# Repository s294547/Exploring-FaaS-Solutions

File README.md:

# EXPLORING FAAS SOLUTION

<div style="margin-left: auto;
            margin-right: auto;
            width: 50%">

|||
|:--:|:--:|
| **Author** | Giulia Bianchi|
| **Contact** | s294547@studenti.polito.it |
</div>

1. [Introduction](#introduction)

## Introduction

This repository, up to now, contains all the data I produced to develop my master thesis. 
Up to now, there are the following folders:
1. [openwhisk](./openwhisk/): it contains whatever I have done related to openwhisk.
2. [microsoft-azure-functions](./microsoft-azure-functions/): it contains whatever I have done/researched related to microsoft azure functions.
3. [AWS-lambda](./AWS-lambda/): it contains whatever I have done/researched related to AWS lambdas.
4. [knative](./knative/): it contains whatever I have done/researched related to knative.
5. [openfaas](./openfaas/):  it contains whatever I have done/researched related to openfaas.
6. [efk](./efk): it contains the informations necessary to develop an efk stack in a kubernetes cluster
7. [helm-charts](./helm-charts): it contains some helm charts.
8. [liquidfaas](./liquidfaas): it contains the KubeConfig file related to the cluster I am using.
9. [SUMMARY](./SUMMARY/): it contains a sumarry of the thesis activity up to now. 
10. [SCHEDA](./SCHEDA/): it contains the files related to the EP8266 board and sensors.

There is another markdown file [discovering-and-comparing-faas-tools](./discovering-and-comparing-faas-tools.md) in which I made a comparison between the analyzed faas tools.

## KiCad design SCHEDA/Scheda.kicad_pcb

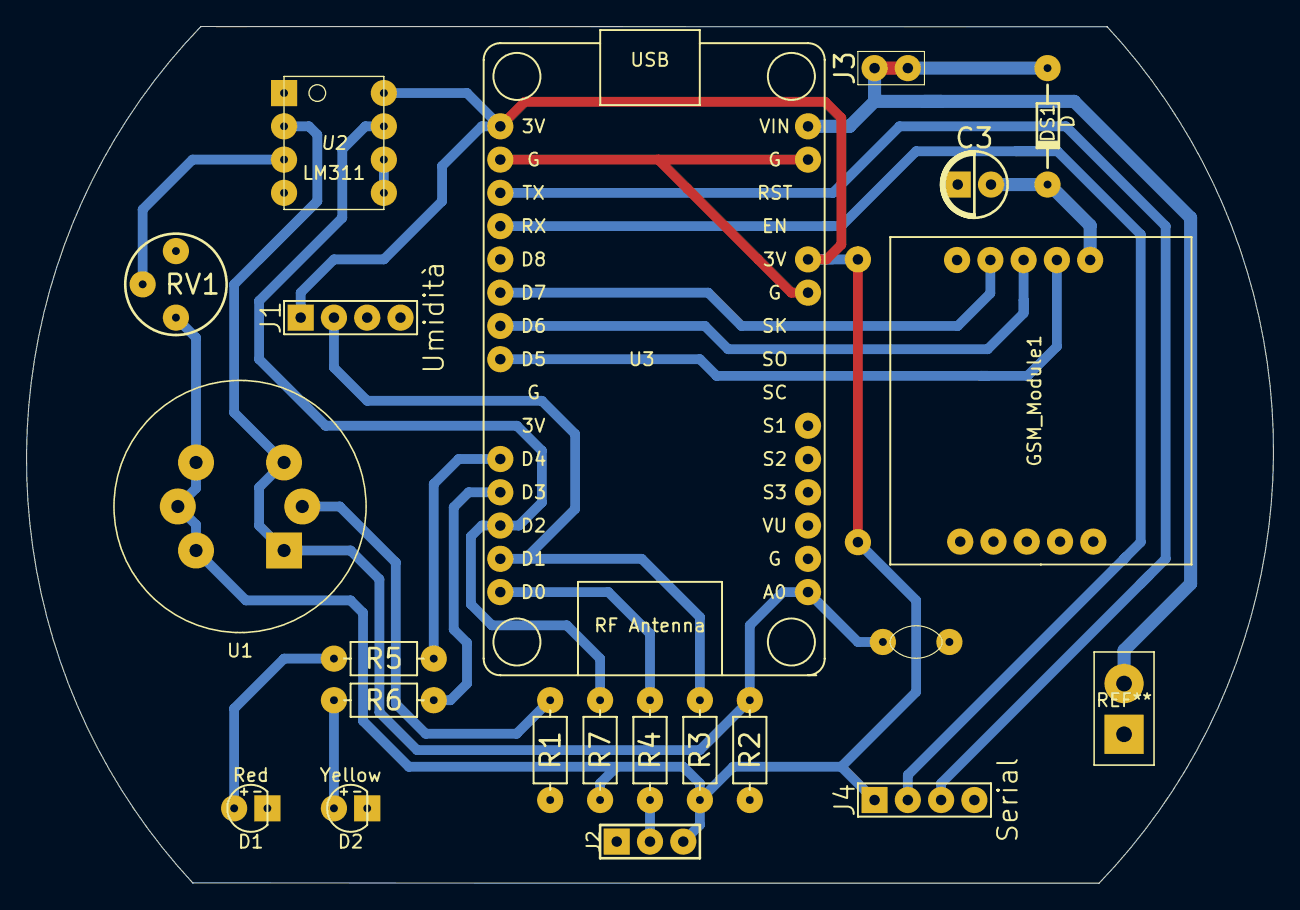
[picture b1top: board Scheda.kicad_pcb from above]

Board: 2 copper layers, 95.2 x 65.4 mm, 21 parts (0 on the bottom side), 21 nets.

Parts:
C1: 104; C_Disc_D5.0mm_W2.5mm_P5.00mm
C3: 470; CP_D5_P2.54
D1: Red; LED_D3.0mm
D2: Yellow; LED_D3.0mm
DS1: D; DO-35
GSM_Module1: SIM800L
J1: Umidità; 1x4-Pin
J2: Selector; 1x3-Pin
J3: Power; 1x2-Pin
J4: Serial; 1x4-Pin
R1: 51; R_P7.62H
R2: 47k; R_P7.62H
R3, R7: 10k; R_P7.62H
R4: 100k; R_P7.62H
R5, R6: 220; R_P7.62H
RV1: TRIM; Bourns_3339H
U1: MQ-6
U2: LM311; DIP-8_W7.62mm_Socket
U3: NodeMCU_1.0_(ESP-12E); ESP12F-Devkit-V3

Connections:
+3V3: J1.1, J2.1, J4.1, R3.1, R7.2, RV1.1, U1.2, U1.4, U1.6, U2.8, U3.11, U3.16
+5V: DS1.2, J3.1, J3.2, U3.15
GND: C1.1, C3.1, D1.2, D2.2, GSM_Module1.6, J1.4, J2.2, J4.4, R1.2, R2.2, RV1.3, U2.1, U2.4, U3.10, U3.14, U3.17
unnamed: C1.2, R2.1, U1.1, U1.3, U2.2, U3.1
unnamed: C3.2, DS1.1, GSM_Module1.2
unnamed: D1.1, R5.2
unnamed: D2.1, R6.2
unnamed: GSM_Module1.3, U3.23
unnamed: GSM_Module1.4, U3.22
unnamed: GSM_Module1.5, U3.21
unnamed: J1.2, R3.2, U3.29
unnamed: J2.3, R4.2
unnamed: J4.2, U3.19
unnamed: J4.3, U3.18
unnamed: R1.1, U1.5
unnamed: R4.1, U3.30
unnamed: R5.1, U3.26
unnamed: R6.1, U3.27
unnamed: R7.1, U2.7, U3.28
unnamed: RV1.2, U2.3
unnamed: U2.5, U2.6

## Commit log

2023-02-14 Added current progresses with OpenWhisk: deployment steps and sample files
2023-02-15 Added the initial version of discovering-and-comparing-faas-tools, a summary of the most important aspects of the FaaS solutions analyzed up to now
2023-02-16 Corrected previous parts about openwhisk and openfaas, added all parts for knative, updated the final matrix
2023-02-16 Added README in openfaas folder, added folder for knative and its documentation in README
2023-02-16 Updated README in knative folder
2023-02-17 Enriched the file discovering-and-comparing-faas-tools.md with sections for AWS Lambda, Google Functions and Azure Functions
2023-02-21 Started to better understand how OpenWhisk works. A documentation of those activity can be found in openwhisk/README.md in the section 'OpenWhisk Deep Dive'
2023-02-21 Removed useless files
2023-02-21 Corrected some paths in openwhisk/README.md
2023-02-22 Still analyzing the resources created after having deployed OpenWhisk
2023-02-24 Deployed EFK stack on the liquidfaas.cloud cluster
2023-02-24 Inspected logs of controller and invoker in openwhisk to better understand what happens when creating an action and invoking it. Added the relative documentation in README.md file in the openwhisk fo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
2023-02-27 Completed the inspection of the logs after creating/invoking/ deleting an action. Added the certificate to be saved in the client machine that talks with openwhisk (the one where we run the command '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
2023-02-28 Started to understand and work with Azure Functions. All the related files are inside the folder 'microsoft-azure-functions', including a README.md file.
2023-03-01 Added informations about Azure Functions (scaling, monitoring and deleting them) in the microsoft-azure-functions/README.md
2023-03-02 Started to understand and work with AWS Lambda Functions. All the related files are inside the folder 'AWS-lambda', including a README.md file.
2023-03-07 Added informations on how to trigger an action in OpenWhisk and a function in Azure after a message has been published on a MQTT topic from an IoT sensor
2023-03-08 Learned about AWS IoT Core. Figured out how to connect an IoT device to the AWS IoT Core and how to trigger a lambda after publishing a message on a topic (all the details are in the MQTT.md file ins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
2023-03-24 Deployed again Openwhisk in order to disable kafka provider and setup an external CouchDB instance for it. Successfully deployed a Mosquitto MQTT broker for a kubernetes cluster and tried to publish/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
2023-03-27 Deployed Influxdb
2023-04-18 Aligning the repository with the current project development
2023-04-18 Removing useless files
2023-04-18 Modified the SUMMARY file
2023-04-19 Added some functionalities to the arduino project that sends telemetry data (sending also the fingerprint and datacenterID). Added an adruino project that sets the datacenterID in the eeprom. Documen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
2023-04-19 Removed junk files
2023-05-08 Aligned repo to last weeks work
2023-05-08 Recovered a lost file
2023-06-07 Updated metrics section
2023-06-07 Minor Updates
2023-06-07 Removed submodules
